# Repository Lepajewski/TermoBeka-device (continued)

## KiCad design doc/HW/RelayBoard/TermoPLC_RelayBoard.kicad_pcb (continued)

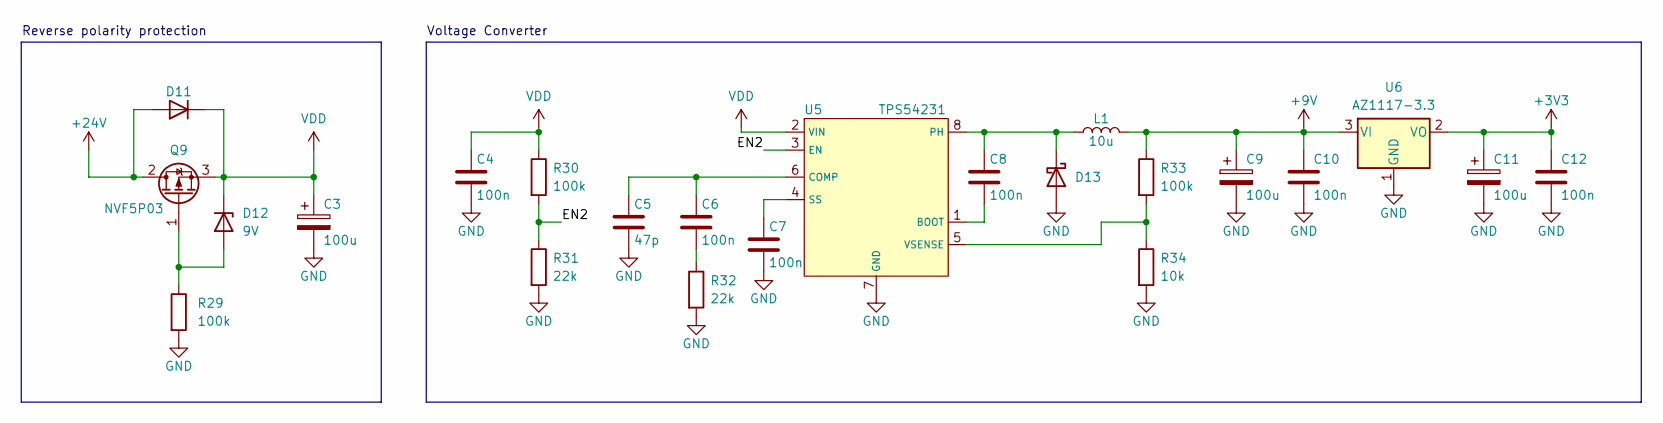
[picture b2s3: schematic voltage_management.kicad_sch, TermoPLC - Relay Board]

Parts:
C3, C9, C11: 100u; CP_Radial_D6.3mm_P2.50mm
C4, C6, C7, C8, C10, C12: 100n; C_0603_1608Metric_Pad1.08x0.95mm_HandSolder
C5: 47p; C_0603_1608Metric_Pad1.08x0.95mm_HandSolder
D11: D; D_MiniMELF
D12: 9V; D_SOD-123
D13: D_Schottky; D_SMA
L1: 10u; L_Bourns_SRN8040TA
Q9: NVF5P03; SOT-223-3_TabPin2
R29, R30, R33: 100k; R_0603_1608Metric_Pad0.98x0.95mm_HandSolder
R31, R32: 22k; R_0603_1608Metric_Pad0.98x0.95mm_HandSolder
R34: 10k; R_0603_1608Metric_Pad0.98x0.95mm_HandSolder
U5: TPS54231; SOIC-8_3.9x4.9mm_P1.27mm
U6: AZ1117-3.3; SOT-223-3_TabPin2

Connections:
+9V: C9.1, C10.1, L1.2, R33.1, U6.3 (VI); also elsewhere on the board
+24V: D11.2 (A), Q9.2 (D); also elsewhere on the board
/Voltage Management/EN2: R30.2, R31.1, U5.3 (EN)
GND: C3.2, C4.2, C5.2, C7.2, C9.2, C10.2, C11.2, C12.2, D13.2 (A), R29.2, R31.2, R32.2, R34.2, U5.7 (GND), U6.1 (GND); also elsewhere on the board
unnamed: C5.1, C6.1, U5.6 (COMP)
unnamed: C6.2, R32.1
unnamed: C7.1, U5.4 (SS)
unnamed: C8.1, D13.1 (K), L1.1, U5.8 (PH)
unnamed: C8.2, U5.1 (BOOT)
unnamed: D12.2 (A), Q9.1 (G), R29.1
unnamed: R33.2, R34.1, U5.5 (VSENSE)
VDD: C3.1, C4.1, D11.1 (K), D12.1 (K), Q9.3 (S), R30.1, U5.2 (VIN)

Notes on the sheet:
Reverse polarity protection
Voltage Converter

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
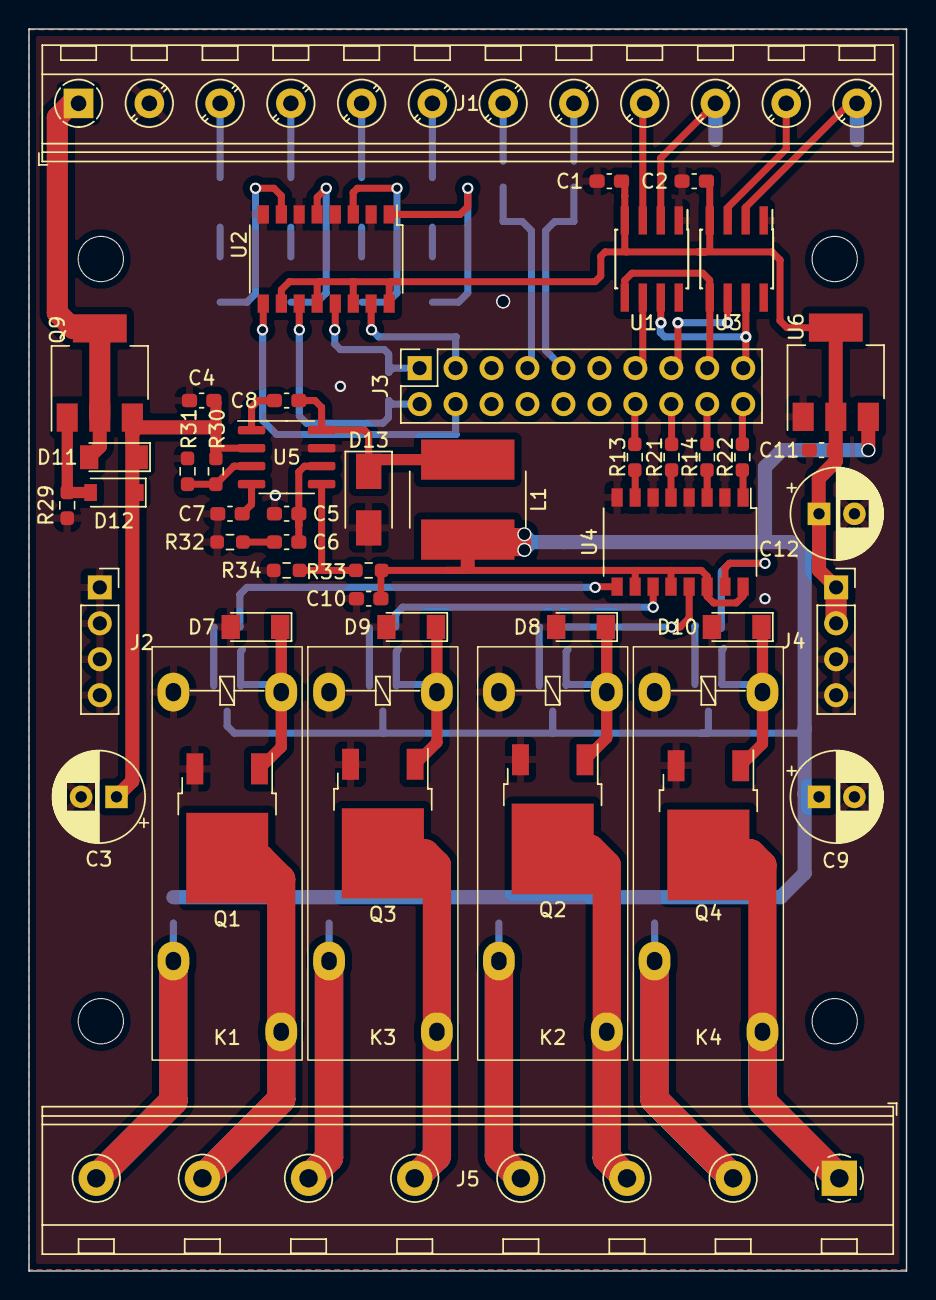
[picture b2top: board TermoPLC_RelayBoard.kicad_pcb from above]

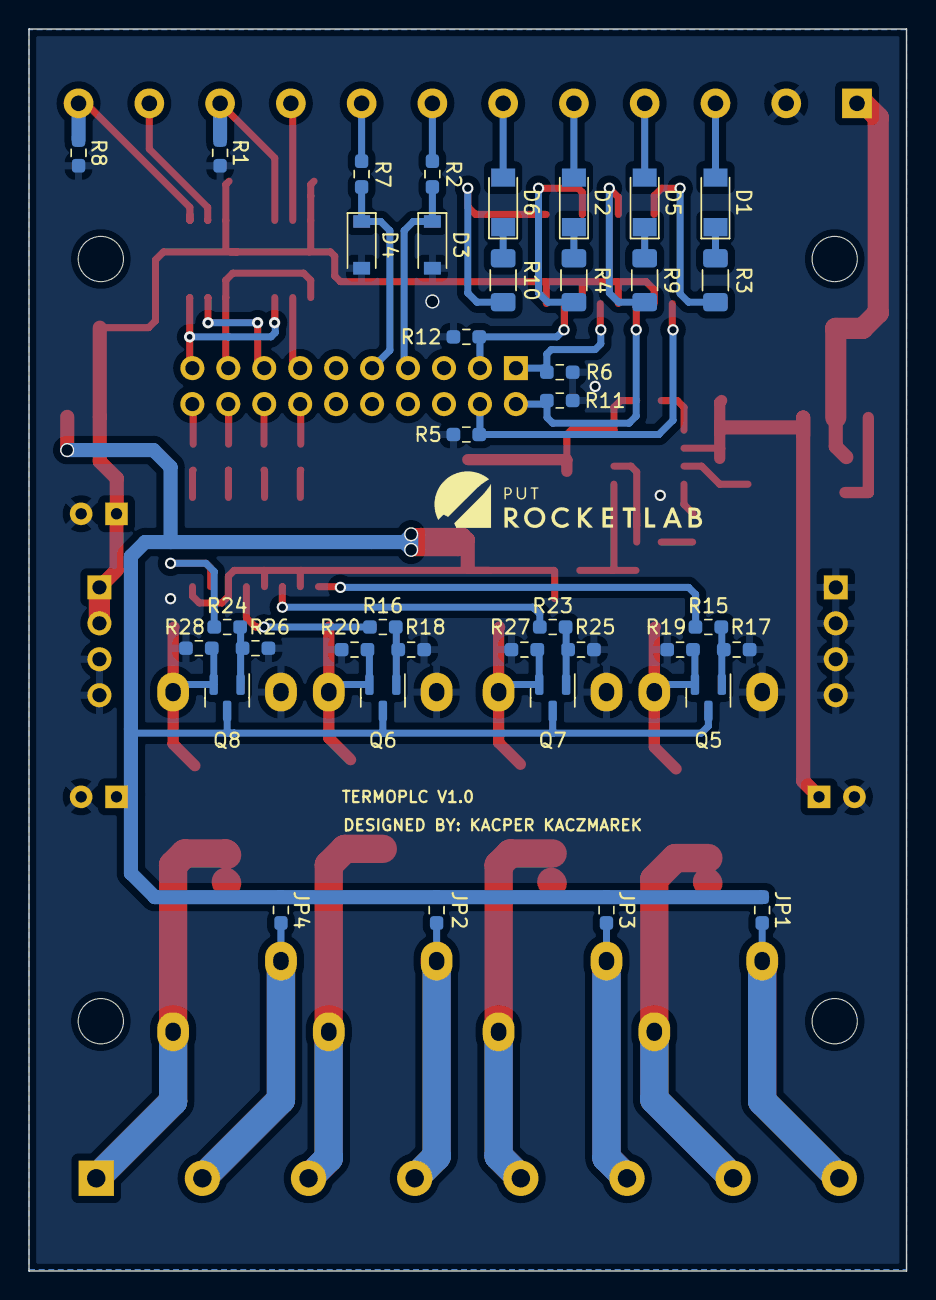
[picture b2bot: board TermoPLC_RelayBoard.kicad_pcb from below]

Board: 2 copper layers, 62.0 x 87.8 mm, 93 parts (39 on the bottom side), 69 nets.

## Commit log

2023-08-21 add build system
2023-09-02 add basic SystemManager with CLI
2023-10-25 add documentation
2023-10-25 update sdkconfig
2023-10-25 set c++17 standard
2023-10-25 minor changes in nvs
2023-10-25 add basic UI Task skeleton
2023-10-25 change to C++23, add basic buzzer driver
2023-10-26 move drivers to separate component, fix: mismatched delete
2023-10-26 change formatting
2023-10-27 add gpio expander driver set pin mode, i2c wrapper
2023-10-27 add polarity settings, refactor
2023-10-28 add GPIOExpander interrupt handling
2023-10-28 remove openthread from menuconfig
2023-10-28 fix: set pin mode only on port0, change: intr to falling edge
2023-10-28 add: set expander to default
2023-10-28 add pin change detect, pca9539 utility macros
2023-11-03 add: button, expander controller class
2023-11-04 add short/long press, fix port bug pca9539 driver
2023-11-04 button callbacks on API layer
2023-11-04 add timer for buzzer
2023-11-05 add LCD driver with API layer
2023-11-05 add RGB leds driver
2023-11-05 update SW architecture schematic
2023-11-05 add: communication layer between SysMgr-UIMgr
2023-11-13 add SD driver, improve commands
2023-11-14 add sd cmd: mkdir, touch rm_file, improve ls
2023-11-16 add cat function
2023-11-17 improve sd mount/unmount
2023-11-17 add save_to_file cmd
2023-11-18 init wifi driver, remove ugly externs
2023-11-18 add NTP
2023-11-19 add wifi manager, wifi cmds
2023-11-19 add wifi scan
2023-11-19 add nvs manager, store & read default config, change wifi mgr behaviour
2023-11-19 Display logo on start
2023-11-21 Create startup and menu scene
2023-11-21 Add missing source in CMakeLists
2023-11-24 update architecture
2023-11-25 improve nvs, change events logic, cleanup
2023-11-25 add partitions table
2023-11-25 move get_timestamp to global
2023-11-25 add wifi reconnect interval & runtime wifi credentials change
2023-11-26 add ETL library
2023-11-26 add profile manager, profile manager task, profile queue, some commands, profile class with timer, profile load, run and end
2023-11-27 Add delta time to update in ui
2023-11-28 Add option list to main menu
2023-11-28 Start working on new lcd controller
2023-11-29 Add initialization code to new lcd controller
2023-12-01 finish going through profile, profile stop & resume
2023-12-01 add: profile update timer, progress %, update event
2023-12-02 add status update to sysmgr
2023-12-02 add profile response event
2023-12-02 add server manager
    add server manager task, few commands, connect, reconnect, auto-connect after wifi connect
2023-12-02 add broker uti to nvs config
2023-12-02 add mqtt uname & pass auth
2023-12-02 Add frame_buf handling
2023-12-02 add MQTT connect over SSL/TLS
2023-12-03 Add draw methods to new lcd controller
2023-12-03 Make the code compile and flash onto the devce
2023-12-03 Fix logo bitmap
2023-12-03 add protobuf, nanopb, publish on profile-update topic
2023-12-03 Add status bar on top of display
2023-12-04 fix NVS config not saving
2023-12-05 Add config.ini reading and parsing
2023-12-06 Add wifi icons
2023-12-06 add CA cert load from SD card, change sysmgr event process
2023-12-07 Make wifi icon functional
2023-12-09 add regulator communication layer, publish status over MQ, read uC temp
2023-12-11 Fix build problems - move rssi to wifi strength calculation to status bar
2023-12-13 Add start profile scene
2023-12-15 Add profile viewing in start profile scene
2023-12-20 Add folder traversing whent selecting profile
2023-12-22 WIP: change proto, reduce MQTT topics to two
2023-12-26 Add showing current path in start profile scene
2023-12-26 Add scrolling directory text to start profile scene
2024-01-03 Add timer to send wifi strength event
2024-01-04 Add csv parser for profiles
2024-01-04 Add button bindings in button.h
2024-01-04 WIP: new PCB software
    buzzer on GPIO expander, add GPIO expanders reset, change pinout to new HW, add MAX31865 library, add OneWire library, add relay controller, fix expander interrupts on port 1, add SPI3 semaphore, tem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
2024-01-04 rebase update
2024-01-04 Add ui_system_state
2024-01-06 new MAX31865 library, rtd controller, reduce proto payload, remove start/stop profile
2024-01-07 Rename scene
2024-01-07 Add selecting profile
2024-01-07 Add profile selected scene
2024-01-08 Make starting and stopping profile functional
2024-01-08 fix MAX31865 vbias
2024-01-11 Fix compilation error
2024-01-11 Add new profile info event
2024-01-11 Add profile bar
2024-01-12 Make scrolling text not scroll
2024-01-12 new proto msgs, profile: start, end, load over MQTT
2024-01-12 fix merge bugs queue sizes
2024-01-12 Fix ui profile not ending
2024-01-12 add profile name send from server to ui, all queues same size
2024-01-12 Fix getting profile name when loading from sd
2024-01-12 Add buzzer when profile ended and on button press
2024-01-13 Fix profile name not showing in loading screen
2024-01-16 Add unmounted sd handling to select profile scene
2024-01-17 Add sd card handling to settings
2024-01-27 regulator from tests
